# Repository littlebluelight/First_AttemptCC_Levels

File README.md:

# First_AttemptCC_Levels
# First_AttemptCC_Levels
# First_AttemptCC_Levels

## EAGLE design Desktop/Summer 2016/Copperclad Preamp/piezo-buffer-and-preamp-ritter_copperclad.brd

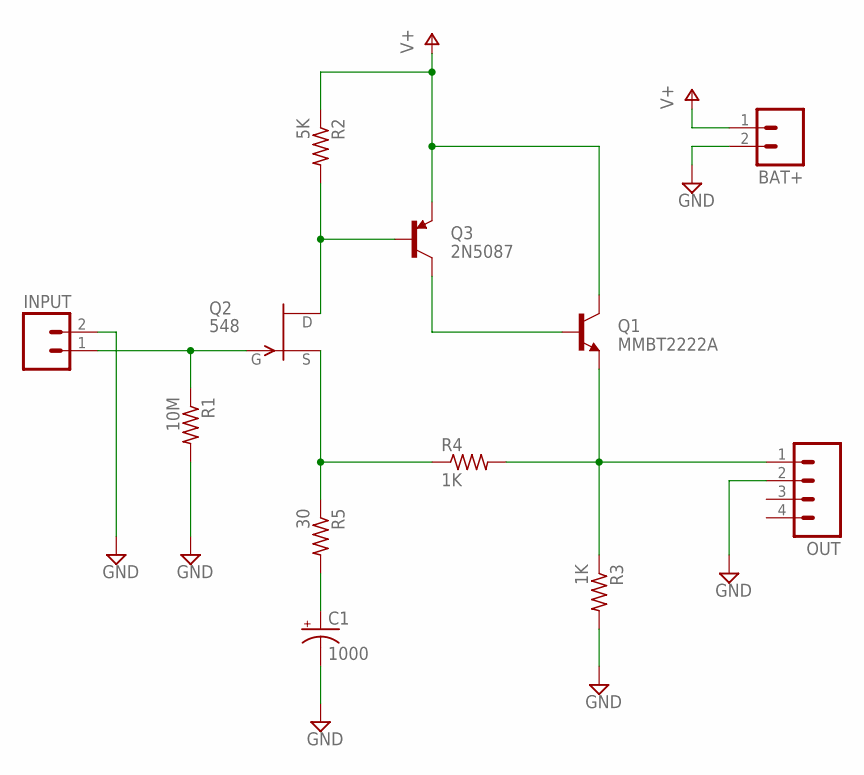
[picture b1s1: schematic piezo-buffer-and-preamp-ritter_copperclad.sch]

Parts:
BAT+: M02LOCK; 1X02_LOCK
C1: 1000; CPOL-RADIAL-10UF-25V
INPUT: M02LOCK; 1X02_LOCK
OUT: M04PTH; 1X04
Q1: MMBT2222A; TO-92
Q2: 548; TO-92
Q3: 2N5087; TO-92
R1: 10M; VMTA55
R2: 5K; VMTA55
R3, R4: 1K; VMTA55
R5: 30; VMTA55

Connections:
GND: BAT+.2, C1.2 (-), INPUT.2, OUT.2, R1.2, R3.2
unnamed: INPUT.1, Q2.1 (G), R1.1
unnamed: Q2.3 (D), Q3.2 (B), R2.2
unnamed: OUT.1, Q1.1 (E), R3.1, R4.2
unnamed: Q2.2 (S), R4.1, R5.1
unnamed: Q1.2 (B), Q3.3 (C)
unnamed: C1.1 (+), R5.2
V+: BAT+.1, Q1.3 (C), Q3.1 (E), R2.1

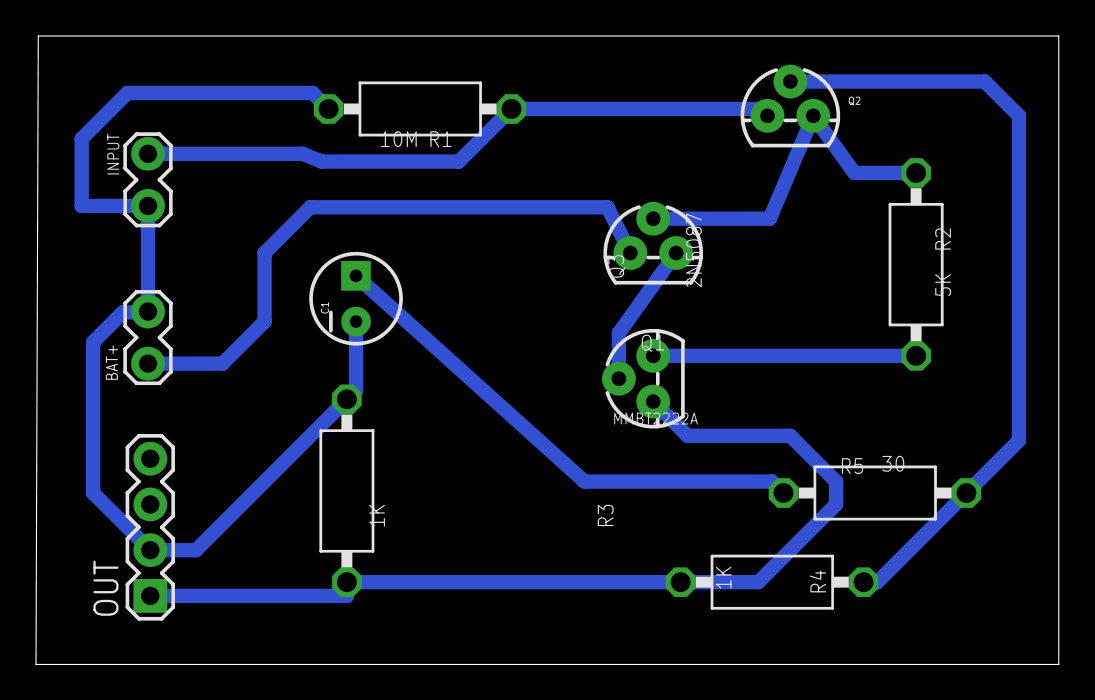
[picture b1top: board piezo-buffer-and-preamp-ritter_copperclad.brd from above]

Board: 2 copper layers, 56.8 x 34.9 mm, 12 parts (0 on the bottom side), 8 nets.

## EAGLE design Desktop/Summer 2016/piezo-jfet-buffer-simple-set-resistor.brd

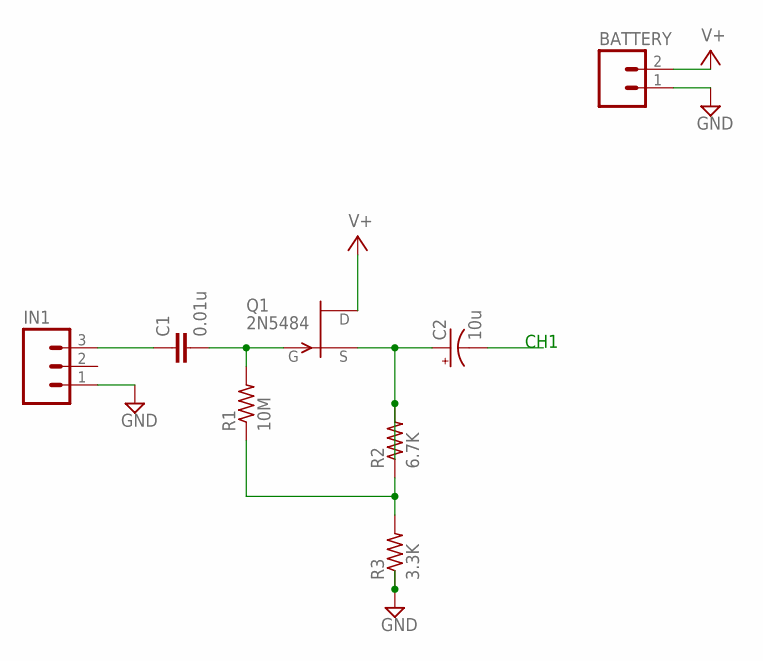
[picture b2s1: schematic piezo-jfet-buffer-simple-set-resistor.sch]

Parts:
BATTERY: M02PTH; 1X02
C1: 0.01u; C5B3
C2: 10u; CPOL-RADIAL-10UF-25V
IN1: M03LOCK; 1X03_LOCK
Q1: 2N5484; TO92-
R1: 10M; 0414V
R2: 6.7K; 0414V
R3: 3.3K; 0414V

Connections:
CH1: C2.2 (-)
GND: BATTERY.1, IN1.1, R3.1
JFET-GATE: C1.2, Q1.1 (G), R1.2
JFET-SOURCE: C2.1 (+), Q1.2 (S), R2.2
unnamed: C1.1, IN1.3
unnamed: R1.1, R2.1, R3.2
V+: BATTERY.2, Q1.3 (D)

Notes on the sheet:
CH1

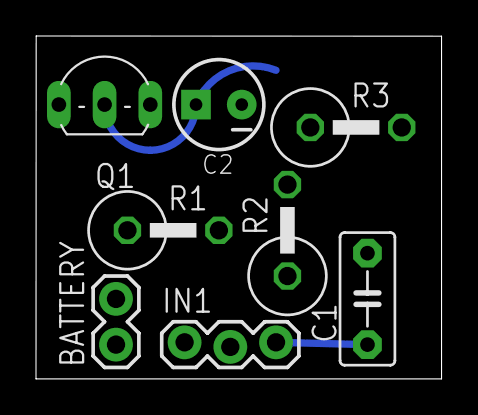
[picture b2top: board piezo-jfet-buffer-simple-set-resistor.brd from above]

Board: 2 copper layers, 22.5 x 19.1 mm, 8 parts (0 on the bottom side), 6 nets.

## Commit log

2016-07-20 updated buffer circuit
2016-07-20 added simple Jack

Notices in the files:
parts and their libraries:
SparkFun-Connectors: Licensing: Creative Commons ShareAlike 4.0 International - https://creativecommons.org/licenses/by-sa/4.0
SparkFun-Connectors: Licensing: CC v3.0 Share-Alike You are welcome to use this library for commercial purposes.
